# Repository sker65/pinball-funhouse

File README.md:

<h1>Funhouse Pinball Extension</h1>

Small project to extend / customize a funhouse pinball maschine with some 
extra light effects and a topper.

An extended version of SoftTimer library is included. It differs from the original
found here https://code.google.com/p/arduino-softtimer/ in that it uses real virtual
methods instead of function pointer. Additionally a task has a state and can be paused
or resumed.

The project / the classes are split in actor classes that control the lamps and leds
and sensor classes that track the connected switches or switched lamps.

Third category of tasks are detection of game modes and controlling actors (not implemented
until now). Everything is modeled as task and can run concurrently to other task.

Looks like this: https://www.youtube.com/watch?v=kvjYMKDT-Vk

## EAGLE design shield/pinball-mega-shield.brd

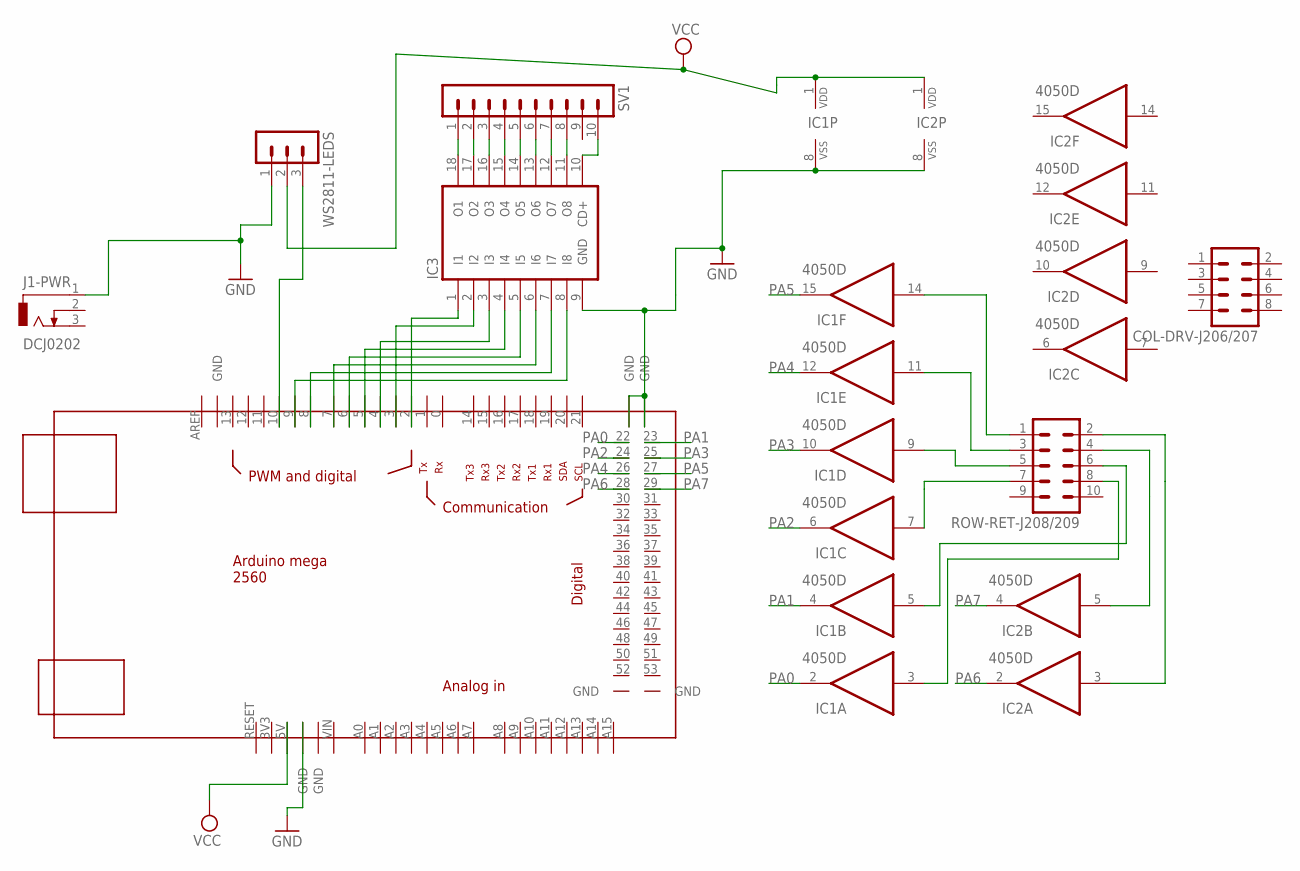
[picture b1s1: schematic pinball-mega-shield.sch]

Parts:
COL-DRV-J206/207: MA04-2
IC1, IC2: 4050D; SO16
IC3: ULN2803A; DIL18
J1-PWR: DCJ0202
ROW-RET-J208/209: MA05-2
SV1: MA10-1
U$1: MEGA_DEVICE; MEGAOUTLINE
WS2811-LEDS: MA03-1

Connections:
GND: IC1.8 (VSS), IC2.8 (VSS), IC3.9 (GND), J1-PWR.1, U$1.GND@2 (GND), U$1.GND@4 (GND), U$1.GND@5 (GND), WS2811-LEDS.1
unnamed: IC1.14 (I), ROW-RET-J208/209.1
unnamed: IC1.11 (I), ROW-RET-J208/209.3
unnamed: IC1.9 (I), ROW-RET-J208/209.5
unnamed: IC1.7 (I), ROW-RET-J208/209.7
unnamed: IC1.3 (I), ROW-RET-J208/209.8
unnamed: IC2.5 (I), ROW-RET-J208/209.4
unnamed: IC2.3 (I), ROW-RET-J208/209.2
unnamed: IC1.5 (I), ROW-RET-J208/209.6
unnamed: U$1.10, WS2811-LEDS.3
unnamed: IC3.18 (O1), SV1.1
unnamed: IC3.17 (O2), SV1.2
unnamed: IC3.16 (O3), SV1.3
unnamed: IC3.15 (O4), SV1.4
unnamed: IC3.14 (O5), SV1.5
unnamed: IC3.13 (O6), SV1.6
unnamed: IC3.12 (O7), SV1.7
unnamed: IC3.11 (O8), SV1.8
unnamed: IC3.10 (CD+), SV1.10
unnamed: IC3.1 (I1), U$1.2
unnamed: IC3.2 (I2), U$1.3
unnamed: IC3.3 (I3), U$1.4
unnamed: IC3.4 (I4), U$1.5
unnamed: IC3.5 (I5), U$1.6
unnamed: IC3.6 (I6), U$1.7
unnamed: IC3.7 (I7), U$1.8
unnamed: IC3.8 (I8), U$1.9
PA0: IC1.2 (O), U$1.22
PA1: IC1.4 (O), U$1.23
PA2: IC1.6 (O), U$1.24
PA3: IC1.10 (O), U$1.25
PA4: IC1.12 (O), U$1.26
PA5: IC1.15 (O), U$1.27
PA6: IC2.2 (O), U$1.28
PA7: IC2.4 (O), U$1.29
VCC: IC1.1 (VDD), IC2.1 (VDD), U$1.5V, WS2811-LEDS.2

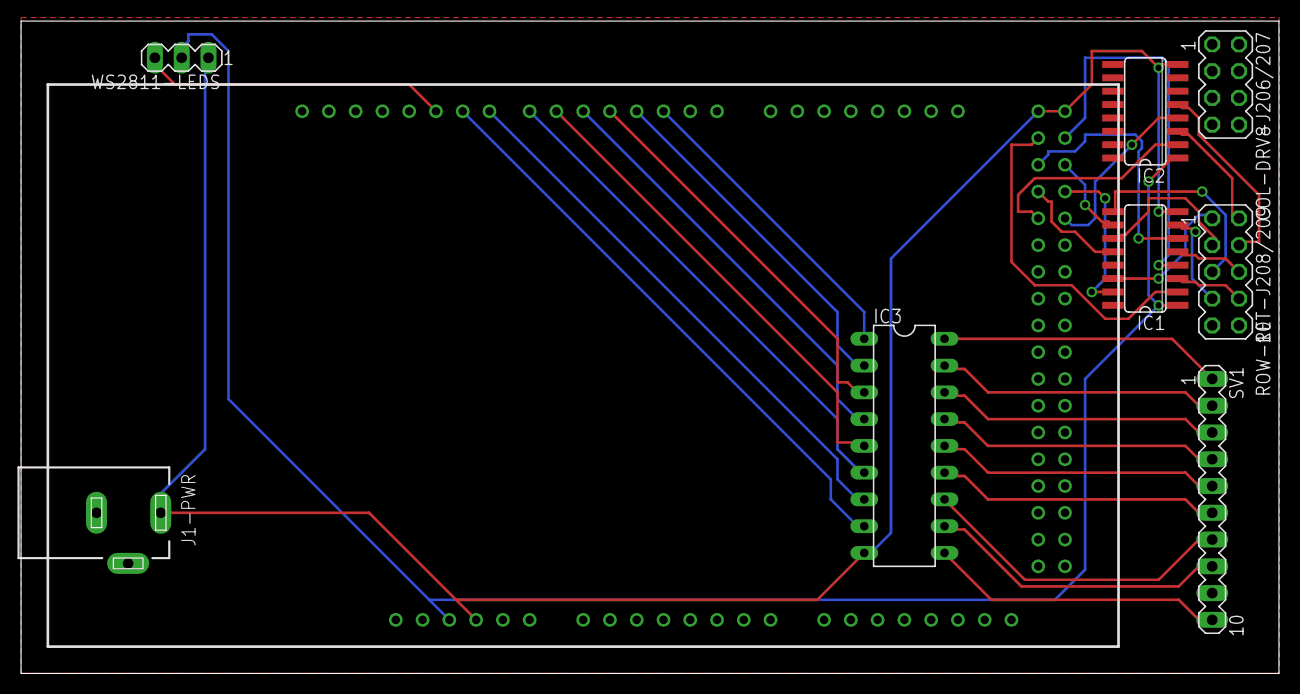
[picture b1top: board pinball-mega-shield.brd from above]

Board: 2 copper layers, 119.4 x 61.9 mm, 9 parts (0 on the bottom side), 36 nets.

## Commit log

2014-10-28 added readme
2014-11-05 - new attract with switiching delay
2014-11-12 - switches added
2014-11-12 - recent changes
2014-11-12 - added ignores
2014-11-12 - Lib und arduino dir
2014-11-12 pins for mega
2014-11-12 Funhouse.ino
2014-11-12 - new mega
2018-05-23 added video link
2018-05-24 - new blink effect
2018-05-24 - latest version of light
2018-05-24 - first draft of shield
